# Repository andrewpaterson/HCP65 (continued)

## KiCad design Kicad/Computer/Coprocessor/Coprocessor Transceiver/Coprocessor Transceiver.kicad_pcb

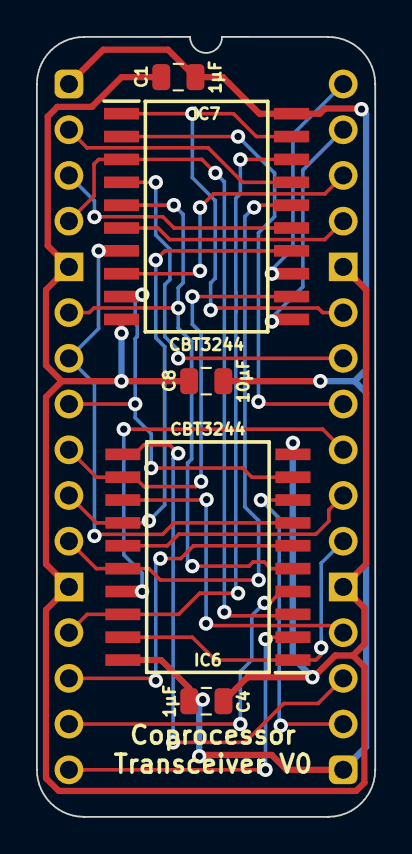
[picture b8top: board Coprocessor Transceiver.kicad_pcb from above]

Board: 2 copper layers, 18.8 x 43.3 mm, 6 parts (0 on the bottom side), 28 nets.

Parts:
C1, C4: 1μF; C_0805
C8: 10µF; C_0805
IC6, IC7: CBT3244AD,112; SOIC127P1032X265-20N
J2: Board 2x16 W15.24mm; DIP-32_Board_W15.24mm

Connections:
5V: C1.1, C4.1, C8.1, IC6.20 (5V), IC7.20 (5V), J2.1, J2.17
DM0: IC6.3 (2B4), IC7.3 (2B4), J2.4
DM1: IC6.5 (2B3), IC7.5 (2B3), J2.6
DM2: IC6.7 (2B2), IC7.7 (2B2), J2.7
DM3: IC6.9 (2B1), IC7.9 (2B1), J2.8
DM4: IC6.12 (1B4), IC7.12 (1B4), J2.9
DM5: IC6.14 (1B3), IC7.14 (1B3), J2.10
DM6: IC6.16 (1B2), IC7.16 (1B2), J2.11
DM7: IC6.18 (1B1), IC7.18 (1B1), J2.13
GND: C1.2, C4.2, C8.2, IC6.10 (GND), IC7.10 (GND), J2.5, J2.12, J2.21, J2.28
M~Memory0•1: IC7.1 (1~OE), IC7.19 (2~OE), J2.27
M~Memory2•3: IC6.1 (1~OE), IC6.19 (2~OE), J2.22
Q0D_{0}: IC7.17 (2A4), J2.2
Q0D_{1}: IC7.15 (2A3), J2.3
Q0D_{2}: IC7.13 (2A2), J2.32
Q0D_{3}: IC7.11 (2A1), J2.31
Q0D_{4}: IC7.8 (1A4), J2.30
Q0D_{5}: IC7.6 (1A3), J2.29
Q0D_{6}: IC7.4 (1A2), J2.26
Q0D_{7}: IC7.2 (1A1), J2.25
Q1D_{0}: IC6.17 (2A4), J2.24
Q1D_{1}: IC6.15 (2A3), J2.23
Q1D_{2}: IC6.13 (2A2), J2.20
Q1D_{3}: IC6.11 (2A1), J2.19
Q1D_{4}: IC6.8 (1A4), J2.18
Q1D_{5}: IC6.6 (1A3), J2.14
Q1D_{6}: IC6.4 (1A2), J2.15
Q1D_{7}: IC6.2 (1A1), J2.16

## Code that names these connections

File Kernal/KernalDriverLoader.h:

#ifndef __KERNAL_DRIVER_LOADER_H__
#define __KERNAL_DRIVER_LOADER_H__
#include "BaseLib/PrimitiveTypes.h"
#include "KernalDriver.h"
#include "KernalMemory.h"


#define KERNAL_DRIVER_DIRECTORY			"\\OS\\Drivers\\"		//Where a board's device ROM's driver file is.
#define KERNAL_DRIVER_ENTRY				"_KernalCreateDriver"	//extern "C" CKernalDriver* KernalCreateDriver(uint16 uiIndex).
#define KERNAL_MAX_MODULES				16						//Different driver files loaded.
#define KERNAL_DRIVER_MEMORY_END		KERNAL_MPU_HEAP_START	//Drivers go in MPU RAM after the kernal, up to its heap.

//What loading a board's driver came to.
#define KERNAL_LOAD_SUCCESS				0
#define KERNAL_LOAD_NOT_FOUND			1		//No such file.
#define KERNAL_LOAD_BAD_FILE			2		//Not a driver module.
#define KERNAL_LOAD_NO_MEMORY			3		//No room in MPU RAM.
#define KERNAL_LOAD_MISSING_EXPORT		4		//It uses a name the kernal doesn't export.
#define KERNAL_LOAD_BAD_RELOCATION		5		//A field it can't be written in where it was put.
#define KERNAL_LOAD_NO_DRIVER			6		//Its create function gave no driver, or the driver couldn't drive the board.
#define KERNAL_LOAD_TOO_MANY			7		//KERNAL_MAX_MODULES driver files are loaded already.


//A name a loaded driver may use and what it is (KernalExports.asm).
struct SKernalExport
{
	const char*	szName;
	void*		pvAddress;
};


//The table (KernalExports.asm): its first byte and how many exports it has.
extern "C" const uint8			gauiKernalExports;
extern "C" const uint16			guiKernalNumExports;


void*	KernalFindExport(const char* szName);
uint16	KernalLoadDriver(uint16 uiSlot);


#endif // __KERNAL_DRIVER_LOADER_H__
